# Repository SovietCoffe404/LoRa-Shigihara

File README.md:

LoRa-Shigihara
This is another HC project; this time it is a LoRa board with an ESP32-S3, SX1262 radio, and U.FL antenna! :D
Made this project because I was a little bit curious 'bout my PCB-Making skills and how to integrate this intoa ESP-32 Marauder

For this project I'm only using KiCad, so I will leave my files right here if u wanna make yours or just take a look to them.

|Name            |Purpose                         |Quantity|Total Cost (USD)|Link                                                                                               |Distributor     |
|----------------|--------------------------------|--------|----------------|---------------------------------------------------------------------------------------------------|----------------|
|PCB             |Having all integrated over there|1       |5.00            |https://jlcpcb.com                                                                                 |JLCPCB          |
|Push Button     |Booting and reset               |2       |6.23            |https://www.amazon.com.mx/pulsador-interruptor-momentáneo-microinterruptor-automático/dp/B0DBGMNQV1|Amazon          |
|5.1K Resistors  |Resistance too                  |2       |0.10            |https://www.digikey.com.mx/es/products/detail/yageo/RC0603FR-135K1L/14008317                       |DigiKey         |
|10k Resistors   |For resistance broo             |2       |0.06            |https://uelectronics.com/producto/resistor-10k-ohm-1-10w-smd-0603-rc0603fr-0710kl/                 |Unit Electronics|
|3.3v Regulator  |For not burning all :)          |1       |0.30            |https://www.digikey.com.mx/es/products/detail/evvo/AMS1117-3.3/22482148                            |DigiKey         |
|15µH Inductor   |aidonnouman                     |1       |0.10            |https://www.digikey.com.mx/es/products/detail/tdk/MLZ2012M150WT000/2465154                         |DigiKey         |
|Capacitor 10µF  |Decoupling                      |2       |0.12            |https://uelectronics.com/producto/capacitor-ceramico-0805-10uf-16v-cl21a106koqnnne/                |Unit Electronics|
|Capacitor 100nF |Decouplin'                      |4       |0.06            |https://uelectronics.com/producto/c0603x104k050t-capacitor-ceramico-0603-100nf-50v/                |Unit Electronics|
|Type C USB      |Powering our board!             |1       |1.01            |https://es.aliexpress.com/item/1005005371954812.html                                               |AliExpress      |
|SX1262          |LoRa Transceiver                |1       |4.67            |https://es.aliexpress.com/item/1005011744738566.html                                               |AliExpress      |
|ESP32-S3-WROOM-1|The brain of our board          |1       |6.32            |https://www.digikey.com.mx/es/products/detail/espressif-systems/ESP32-S3-WROOM-1U-N8R8/16162638    |DigiKey         |

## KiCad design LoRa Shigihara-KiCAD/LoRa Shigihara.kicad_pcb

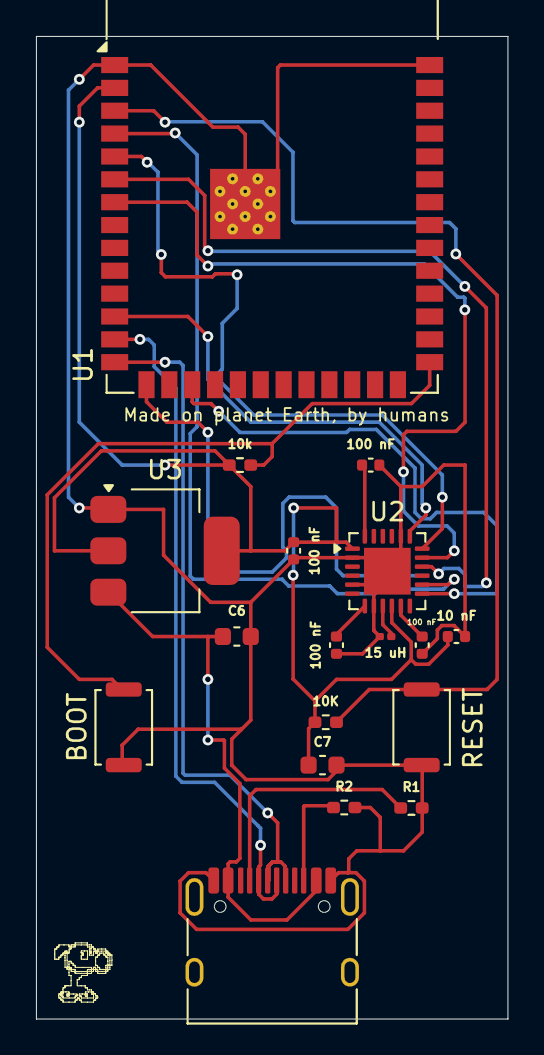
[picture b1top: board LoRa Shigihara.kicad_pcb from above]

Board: 2 copper layers, 26.2 x 54.6 mm, 18 parts (0 on the bottom side), 20 nets.

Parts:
10 nF: 10 nf; C_0402_1005Metric
10K, 10k: R; R_0402_1005Metric_Pad0.72x0.64mm_HandSolder
15 uH: 15 uH; L_0201_0603Metric
100 nF, 100 nF#2, 100 nF#3, 100 nF#4: 100 nf; C_0402_1005Metric
BOOT: SW_Push; SW_Push_SPST_NO_Alps_SKRK
C6, C7: 10uf; C_0603_1608Metric
J1: USB_C_Receptacle_USB2.0_14P; USB_C_Receptacle_HRO_TYPE-C-31-M-12
R1, R2: 5.1k; R_0402_1005Metric_Pad0.72x0.64mm_HandSolder
RESET: SW_Push; SW_Push_SPST_NO_Alps_SKRK
U1: ESP32-S3-WROOM-1
U2: SX1262IMLTRT; QFN-24-1EP_4x4mm_P0.5mm_EP2.6x2.6mm
U3: AMS1117-3.3; SOT-223-3_TabPin2

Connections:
+3.3V: 10 nF.1, 10K.1, 10k.1, 100 nF#3.1, C7.1, U1.2 (3V3), U2.1 (VDD_IN), U2.10 (VBAT), U3.2 (VO)
+5V: C6.1, J1.A4 (VBUS), J1.A9 (VBUS), J1.B4 (VBUS), J1.B9 (VBUS), U3.3 (VI)
BUSY: U1.4 (IO4), U2.14 (BUSY)
DIO1: U1.17 (IO9), U2.13 (DIO1)
GND: 10 nF.2, 15 uH.2, 100 nF.1, 100 nF#2.2, 100 nF#3.2, 100 nF#4.1, BOOT.1, C6.2, C7.2, J1.A1 (GND), J1.A12 (GND), J1.B1 (GND), J1.B12 (GND), R1.2, R2.2, RESET.1, U1.1 (GND), U1.40 (GND), U1.41 (GND), U2.2 (GND), U2.5 (GND), U2.8 (GND), U2.20 (GND), U2.25 (GND), U3.1 (GND)
MISO: U1.6 (IO6), U2.16 (MISO)
MOSI: U1.7 (IO7), U2.17 (MOSI)
NSS: U1.12 (IO8), U2.19 (NSS)
unnamed: J1.A5 (CC1), R1.1
unnamed: J1.B5 (CC2), R2.1
unnamed: 10K.2, RESET.2, U1.3 (EN)
unnamed: 10k.2, BOOT.2, U1.27 (IO0)
unnamed: 15 uH.1, U2.9 (DCC_SW)
unnamed: 100 nF#4.2, U2.11 (VBAT_IO)
unnamed: 100 nF.2, U2.7 (VREG)
unnamed: 100 nF#2.1, U2.24 (VR_PA)
RST: U1.15 (IO3), U2.15 (~RESET)
SCK: U1.5 (IO5), U2.18 (SCK)
USB +: J1.A6 (D+), J1.B6 (D+), U1.14 (USB_D+)
USB -: J1.A7 (D-), J1.B7 (D-), U1.13 (USB_D-)

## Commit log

2026-05-08 Add project description for LoRa-Shigihara
2026-05-17 Add project images to README
    Added images to README for project visualization.
2026-06-17 Revise component list and update costs
    Updated component list with new PCB entry and adjusted costs.
